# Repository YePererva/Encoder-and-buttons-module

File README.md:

# Rotary encoder and Push-Buttons module with hardware debouncing

Module provides rotary encoder and 3 push-buttons with debouncing circuitry, based on 74xx14 inverting Schmitt trigger.

## Dimensions and layout

- overall dimensions: 1.0 in × 2.5 in
- mounting holes spacing : 0.75 in × 2.25 in
- mounting holes size : M3
- SMD sized:
	- Resistors: 0805
	- Capacitors : 0805
	- Diodes : MiniMELF

| Top View | Bottom View |
| ------ | ------|
|  |  |

## Schematics origin

Schematics is based on [this](https://my.eng.utah.edu/~cs5780/debouncing.pdf) work and is adjusted for:
- having both 1 rotary incremental encoder and 3 push buttons
- ability to solder eitehr SMD or DIP version of 74xx14 IC
- having option to push into breadboard or mount somewhere via mounting holes

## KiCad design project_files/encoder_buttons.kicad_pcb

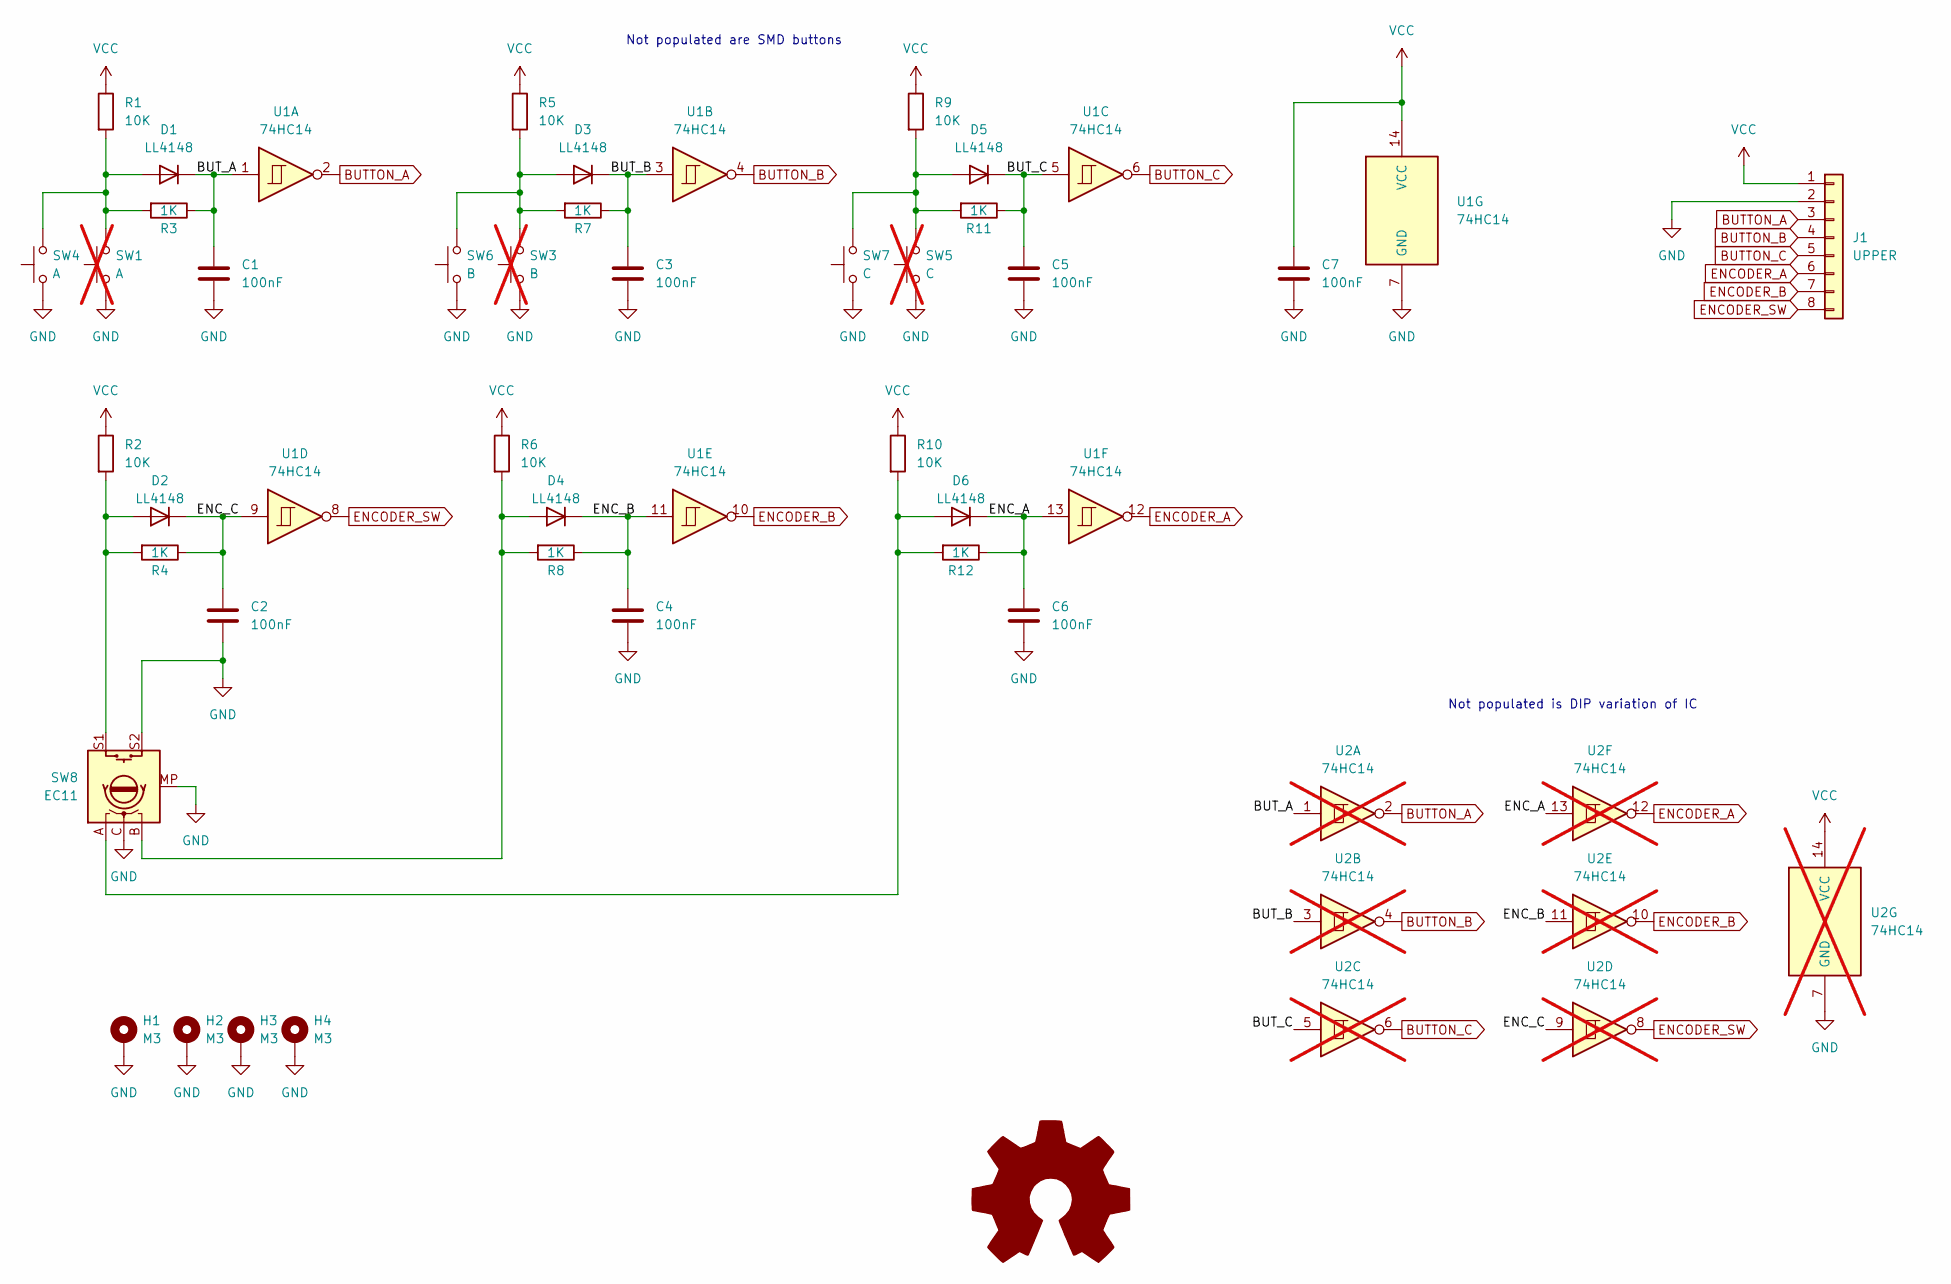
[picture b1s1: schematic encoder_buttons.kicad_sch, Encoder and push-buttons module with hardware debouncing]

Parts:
C1, C2, C3, C4, C5, C6, C7: 100nF; C_0805_2012Metric
D1, D2, D3, D4, D5, D6: LL4148; D_MiniMELF
H1, H2, H3, H4: M3; MountingHole_3.2mm_M3_DIN965_Pad_TopBottom
J1: UPPER; PinHeader_1x08_P2.54mm_Vertical
R1, R2, R5, R6, R9, R10: 10K; R_0805_2012Metric
R3, R4, R7, R8, R11, R12: 1K; R_0805_2012Metric
SW1: A; SW_SPST_PTS645; not fitted
SW3: B; SW_SPST_PTS645; not fitted
SW4: A; SW_PUSH_6mm
SW5: C; SW_SPST_PTS645; not fitted
SW6: B; SW_PUSH_6mm
SW7: C; SW_PUSH_6mm
SW8: EC11; RotaryEncoder_Alps_EC11E-Switch_Vertical_H20mm
U1: 74HC14; SO-14_3.9x8.65mm_P1.27mm
U2: 74HC14; DIP-14_W7.62mm; not fitted

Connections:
/BUT_A: C1.1, D1.1 (K), R3.1, U1.1, U2.1
/BUT_B: C3.1, D3.1 (K), R7.1, U1.3, U2.3
/BUT_C: C5.1, D5.1 (K), R11.1, U1.5, U2.5
/ENC_A: C6.1, D6.1 (K), R12.1, U1.13, U2.13
/ENC_B: C4.1, D4.1 (K), R8.1, U1.11, U2.11
/ENC_C: C2.1, D2.1 (K), R4.1, U1.9, U2.9
BUTTON_A: J1.3, U1.2, U2.2
BUTTON_B: J1.4, U1.4, U2.4
BUTTON_C: J1.5, U1.6, U2.6
ENCODER_A: J1.6, U1.12, U2.12
ENCODER_B: J1.7, U1.10, U2.10
ENCODER_SW: J1.8, U1.8, U2.8
GND: C1.2, C2.2, C3.2, C4.2, C5.2, C6.2, C7.2, H1.1, H2.1, H3.1, H4.1, J1.2, SW1.1, SW3.1, SW4.1, SW5.1, SW6.1, SW7.1, SW8.C, SW8.MP, SW8.S2, U1.7 (GND), U2.7 (GND)
unnamed: D1.2 (A), R1.2, R3.2, SW1.2, SW4.2
unnamed: D2.2 (A), R2.2, R4.2, SW8.S1
unnamed: D3.2 (A), R5.2, R7.2, SW3.2, SW6.2
unnamed: D4.2 (A), R6.2, R8.2, SW8.B
unnamed: D5.2 (A), R9.2, R11.2, SW5.2, SW7.2
unnamed: D6.2 (A), R10.2, R12.2, SW8.A
VCC: C7.1, J1.1, R1.1, R2.1, R5.1, R6.1, R9.1, R10.1, U1.14 (VCC), U2.14 (VCC)

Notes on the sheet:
Not populated is DIP variation of IC
Not populated are SMD buttons

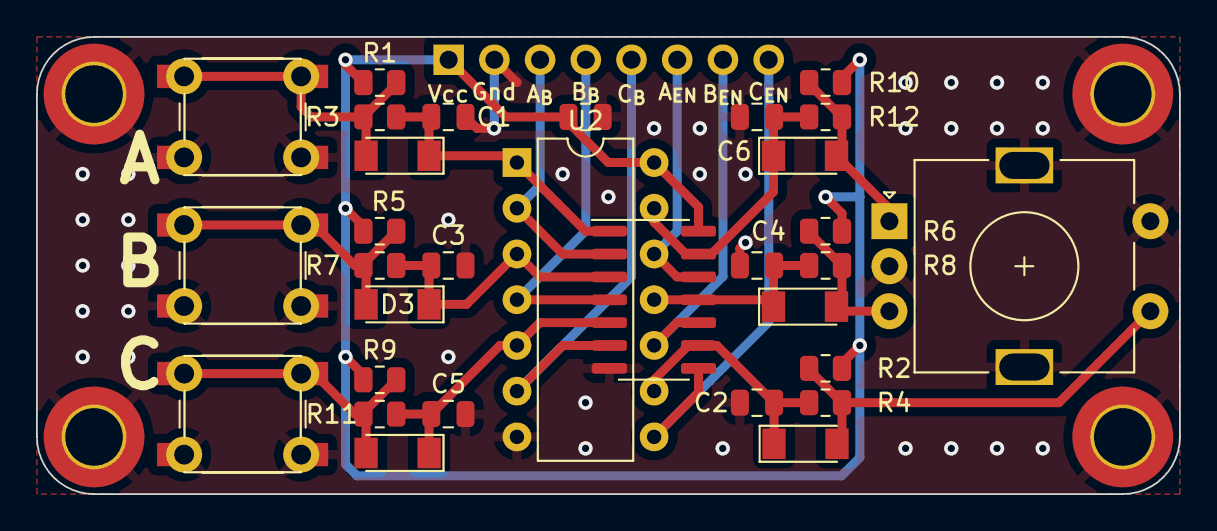
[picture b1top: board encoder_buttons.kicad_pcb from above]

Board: 2 copper layers, 63.5 x 25.4 mm, 39 parts (1 on the bottom side), 20 nets.

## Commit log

2022-08-28 initial thoughts
2024-05-29 Reopened in Kicad 8
2024-05-29 placing the components
2024-05-29 minor edits
2024-05-29 Finalized and rendered
2024-05-29 Added Readme and Dimensions
2024-05-29 Fixed folders names
2024-06-01 Re-routed with wider traces
